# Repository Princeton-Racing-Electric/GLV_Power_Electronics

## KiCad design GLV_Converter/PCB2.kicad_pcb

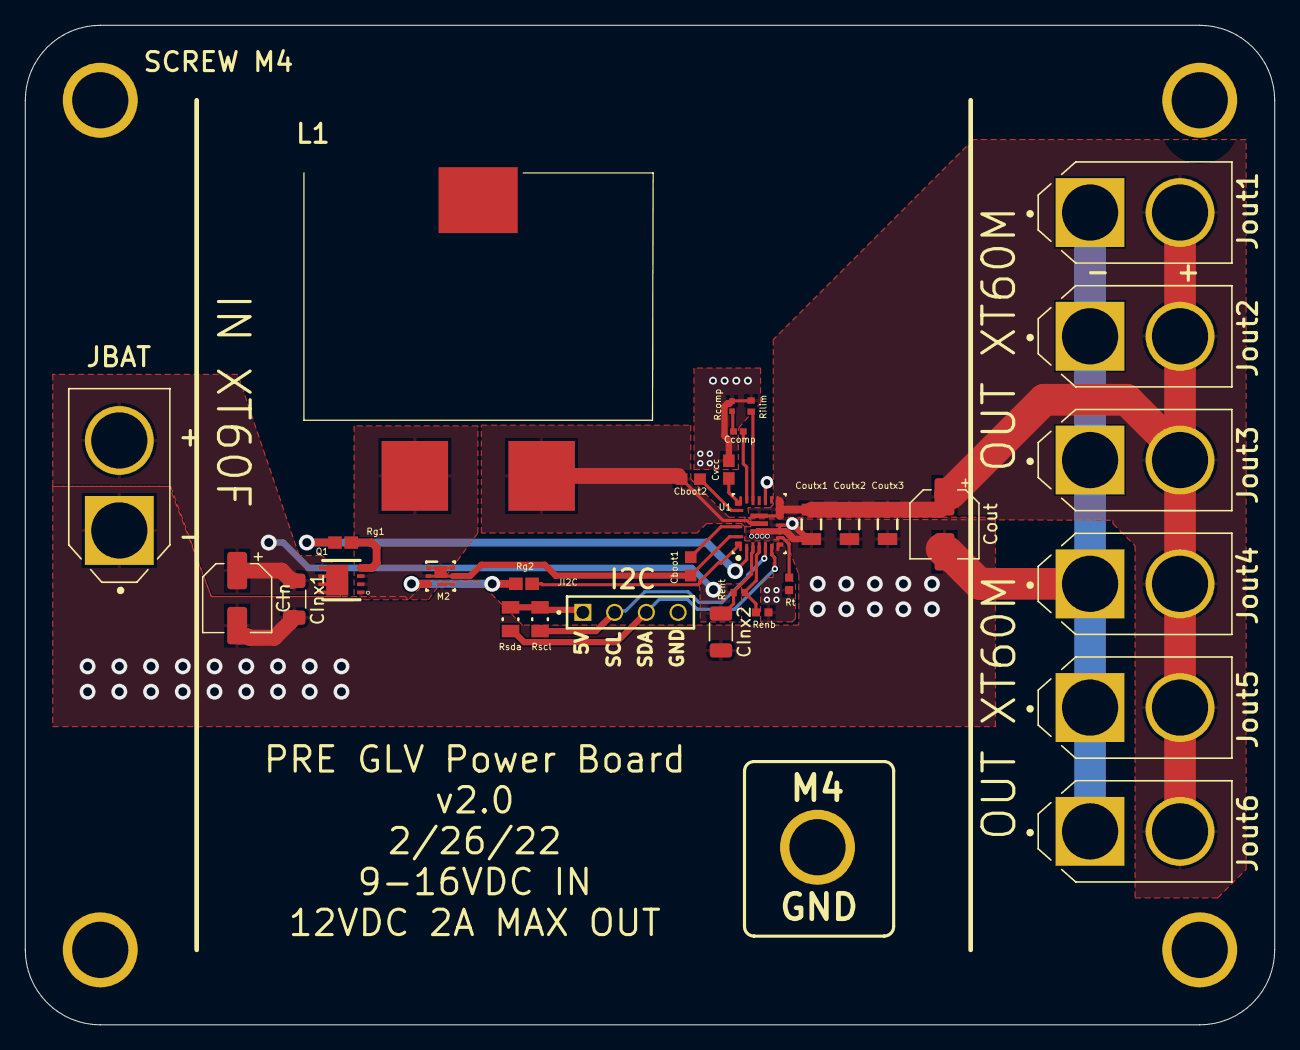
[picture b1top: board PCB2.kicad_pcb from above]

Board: 2 copper layers, 100.0 x 80.0 mm, 32 parts (0 on the bottom side), 20 nets.

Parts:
CIn: 20SVF56M; CP_Elec_5x5.9
CInx1, CInx2: GRM31CR71E475KA88L; C_1206_3216Metric
Cboot1, Cboot2: EMK107B7104KA-T; CAPC1608X90N
Ccomp: GRM155R71C472KA01D; CAPC1005X55X25LL05T10
Cout: 20SVF56M; CP_Elec_5x5.9
Coutx1, Coutx2, Coutx3: C2012X7S1E106K125AC; FP-C2012-125-IPC_A
Cvcc: C1608X6S1C475K080AC; CAPC1608X90N
JBAT: XT60-M; AMASS_XT60-M
JI2C: TSW-104-26-F-S; SAMTEC_TSW-104-26-F-S
Jout1, Jout2, Jout3, Jout4, Jout5, Jout6: XT60-M; AMASS_XT60-M
L1: PQ2614BLA-100K; PQ2614BLA100K
M2: CSD16301Q2; DQK0006C
Q1: CSD17577Q3A; Q3A
Rcomp: CRCW040247K5FKTD; RESC1005X40X25LL05T05
Renb: CRCW0402100KFKTD; RESC1005X40X25ML05T05
Rent: CRCW0402634KFKED; RESC1005X40N
Rg1, Rg2: RC0603FR-071RL; RESC1608X55N
Rilim: RMCF0402FT21K0; RESC1005X40N
Rscl: CRCW08054K70FKEA; FP-CRCW0805-e3-IPC_B
Rsda: CRCW08054K70FKEA; FP-CRCW0805-e3-IPC_B
Rt: CRCW040266K5FKED; RESC1005X40X25ML05T05
U1: TPS55288QRPMRQ1; RPM0026A-MFG

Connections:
GND: CIn.2, CInx1.2, CInx2.2, Cout.2, Coutx1.2, Coutx2.2, Coutx3.2, Cvcc.1, JBAT.1, JI2C.04, Jout1.1, Jout2.1, Jout3.1, Jout4.1, Jout5.1, Jout6.1, M2.4, M2.7, Rcomp.1, Renb.1, Rilim.2, Rt.1, U1.7, U1.9, U1.10, U1.15, U1.24
NetCboot1_1: Cboot1.1, L1.1, M2.1, M2.2, M2.5, M2.6, M2.8, Q1.1, Q1.2, Q1.3, U1.23
NetCboot1_2: Cboot1.2, U1.22
NetCboot2_1: Cboot2.1, U1.20
NetCboot2_2: Cboot2.2, L1.3, U1.21, U1.25
NetCcomp_1: Ccomp.1, Rcomp.2
NetCcomp_2: Ccomp.2, U1.18
NetCout_1: Cout.1, Coutx1.1, Coutx2.1, Coutx3.1, Jout1.2, Jout2.2, Jout3.2, Jout4.2, Jout5.2, Jout6.2, U1.11, U1.12, U1.13, U1.26
NetCvcc_2: Cvcc.2, U1.19
NetJI2C_01: JI2C.01, Rscl.1, Rsda.1
NetJI2C_02: JI2C.02, Rscl.2, U1.5
NetJI2C_03: JI2C.03, Rsda.2, U1.6
NetM2_3: M2.3, Rg2.1
NetQ1_4: Q1.4, Rg1.1
NetRenb_2: Renb.2, Rent.1, U1.4
NetRg1_2: Rg1.2, U1.2
NetRg2_2: Rg2.2, U1.1
NetRilim_1: Rilim.1, U1.17
NetRt_2: Rt.2, U1.8
VCC: CIn.1, CInx1.1, CInx2.1, JBAT.2, Q1.5, Q1.6, Q1.7, Q1.8, Rent.2, U1.3

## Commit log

2022-03-01 Push converter
